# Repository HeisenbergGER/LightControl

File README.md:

# LightControl
Here you can find all project files for the LightControl Project, including schematics, PCB-designs, fabrication files and renderings.

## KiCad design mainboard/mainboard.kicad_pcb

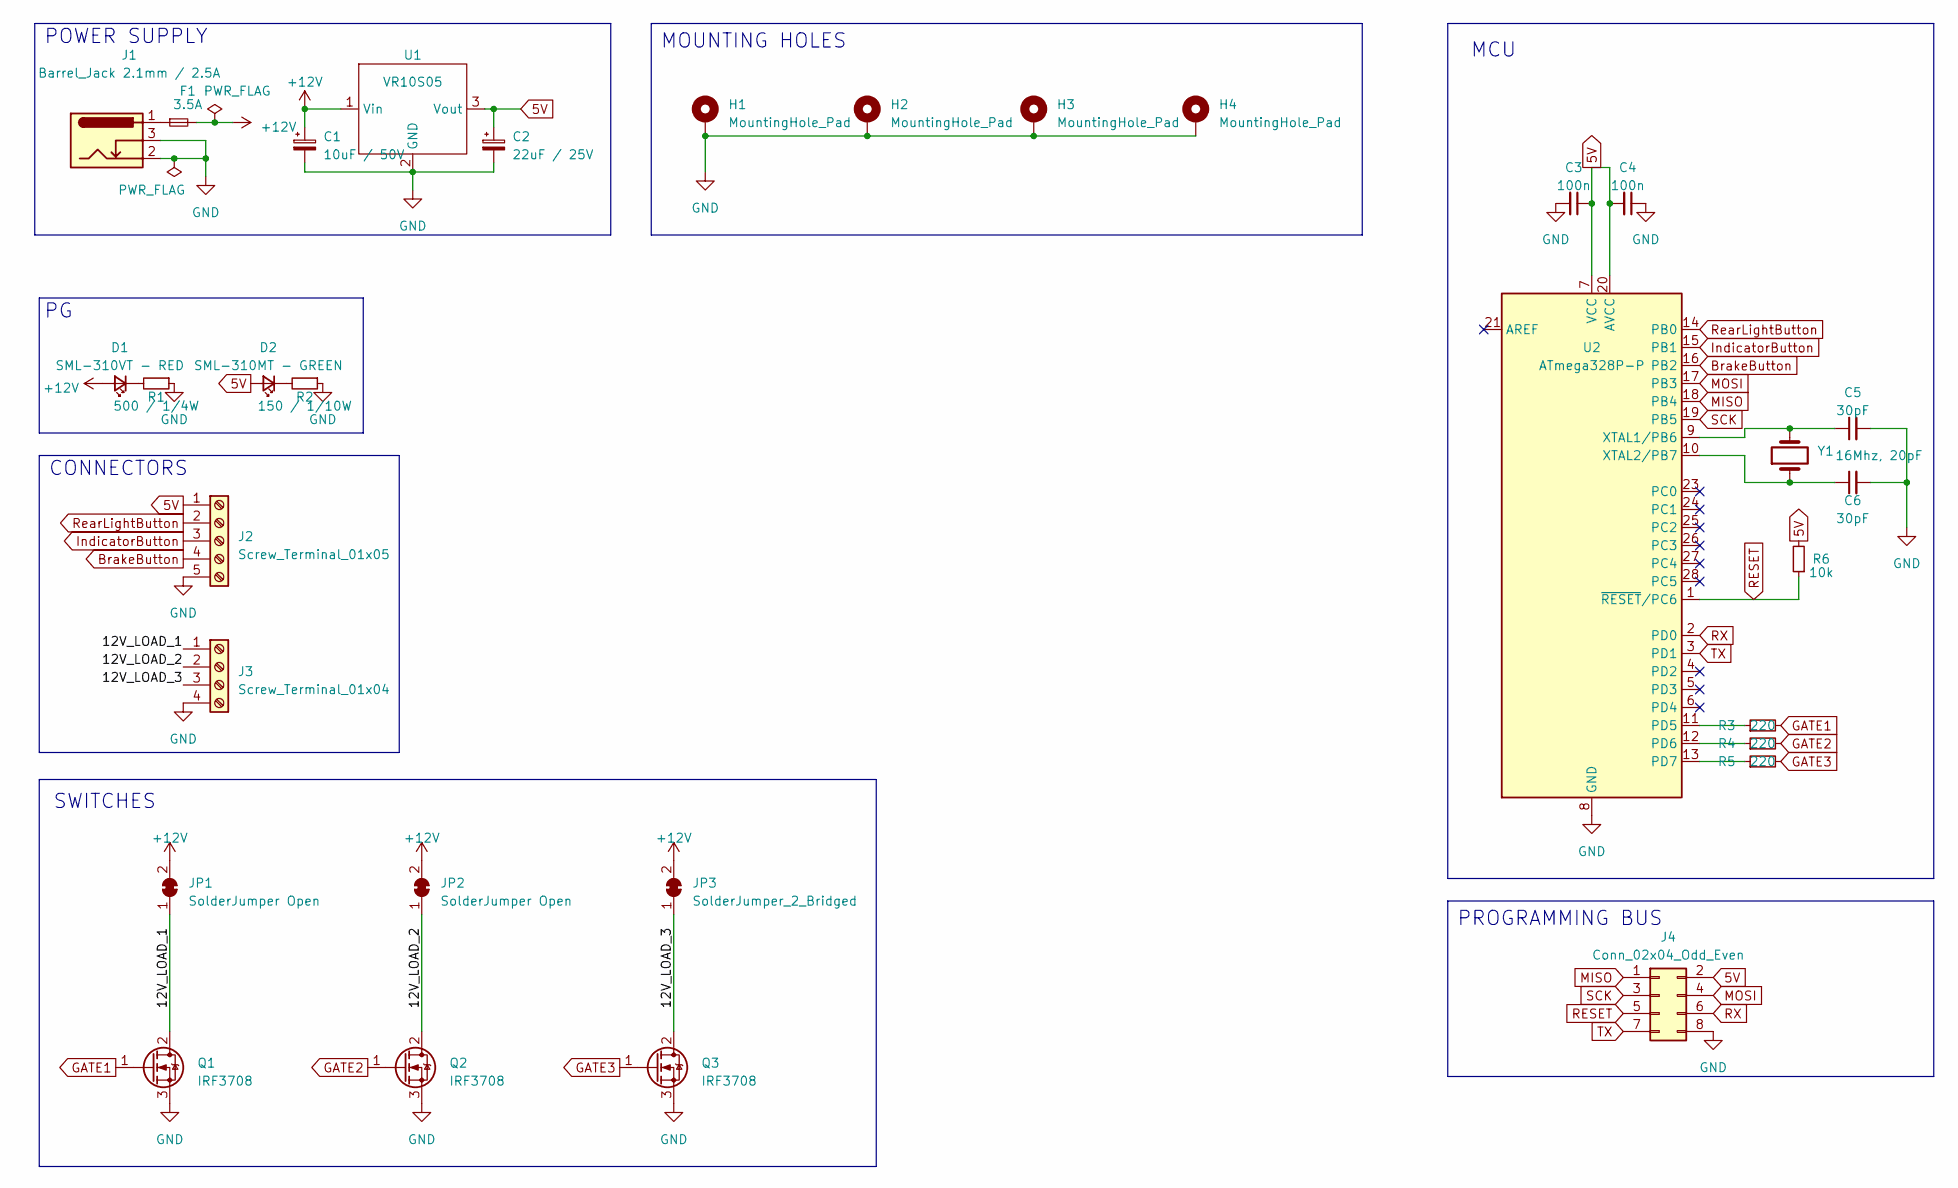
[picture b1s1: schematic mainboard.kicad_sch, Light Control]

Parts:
C1: 10uF / 50V; C_Radial_D5.0mm_H5.0mm_P2.00mm
C2: 22uF / 25V; C_Radial_D5.0mm_H5.0mm_P2.00mm
C3, C4: 100n; C_0603_1608Metric
C5, C6: 30pF; C_0603_1608Metric
D1: SML-310VT - RED; LED_0603_1608Metric
D2: SML-310MT - GREEN; LED_0603_1608Metric
F1: 3.5A; R_1206_3216Metric
H1, H2, H3, H4: MountingHole_Pad; MountingHole_3.2mm_M3_DIN965_Pad
J1: Barrel_Jack 2.1mm / 2.5A; CUI_PJ-202B
J2: Screw_Terminal_01x05; TerminalBlock_TE_282834-5_1x05_P2.54mm_Horizontal
J3: Screw_Terminal_01x04; TerminalBlock_TE_282834-4_1x04_P2.54mm_Horizontal
J4: Conn_02x04_Odd_Even; PinHeader_2x04_P2.54mm_Vertical
JP1, JP2: SolderJumper Open; SolderJumper-2_P1.3mm_Open_TrianglePad1.0x1.5mm
JP3: SolderJumper_2_Bridged; SolderJumper-2_P1.3mm_Open_TrianglePad1.0x1.5mm
Q1, Q2, Q3: IRF3708; TO-220-3_Vertical
R1: 500 / 1/4W; R_0603_1608Metric
R2: 150 / 1/10W; R_0603_1608Metric
R3, R4, R5: 220; R_0603_1608Metric
R6: 10k; R_0603_1608Metric
U1: VR10S05; SIP3_11.6x8.5mm
U2: ATmega328P-P; DIP-28_W7.62mm
Y1: 16Mhz, 20pF; Crystal_HC49-4H_Vertical

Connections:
5V: C2.1, C3.1, C4.2, D2.2 (A), J2.1, J4.2, R6.2, U1.3 (Vout), U2.7 (VCC), U2.20 (AVCC)
+12V: C1.1, D1.2 (A), F1.2, JP1.2 (B), JP2.2 (B), JP3.2 (B), U1.1 (Vin)
/12V_LOAD_1: J3.1, JP1.1 (A), Q1.2 (D)
/12V_LOAD_2: J3.2, JP2.1 (A), Q2.2 (D)
/12V_LOAD_3: J3.3, JP3.1 (A), Q3.2 (D)
BrakeButton: J2.4, U2.16 (PB2)
GATE1: Q1.1 (G), R3.2
GATE2: Q2.1 (G), R4.2
GATE3: Q3.1 (G), R5.2
GND: C1.2, C2.2, C3.2, C4.1, C5.2, C6.2, H1.1, H2.1, H3.1, H4.1, J1.2, J1.3, J2.5, J3.4, J4.8, Q1.3 (S), Q2.3 (S), Q3.3 (S), R1.1, R2.1, U1.2 (GND), U2.8 (GND), U2.22 (GND)
IndicatorButton: J2.3, U2.15 (PB1)
MISO: J4.1, U2.18 (PB4)
MOSI: J4.4, U2.17 (PB3)
unnamed: D1.1 (K), R1.2
unnamed: D2.1 (K), R2.2
unnamed: F1.1, J1.1
unnamed: R3.1, U2.11 (PD5)
unnamed: R4.1, U2.12 (PD6)
unnamed: R5.1, U2.13 (PD7)
unnamed: C5.1, U2.9 (XTAL1/PB6), Y1.2
unnamed: C6.1, U2.10 (XTAL2/PB7), Y1.1
RESET: J4.5, R6.1, U2.1 (~RESET/PC6)
RX: J4.6, U2.2 (PD0)
RearLightButton: J2.2, U2.14 (PB0)
SCK: J4.3, U2.19 (PB5)
TX: J4.7, U2.3 (PD1)

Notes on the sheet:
PROGRAMMING BUS
CONNECTORS
POWER SUPPLY
MOUNTING HOLES
SWITCHES
MCU

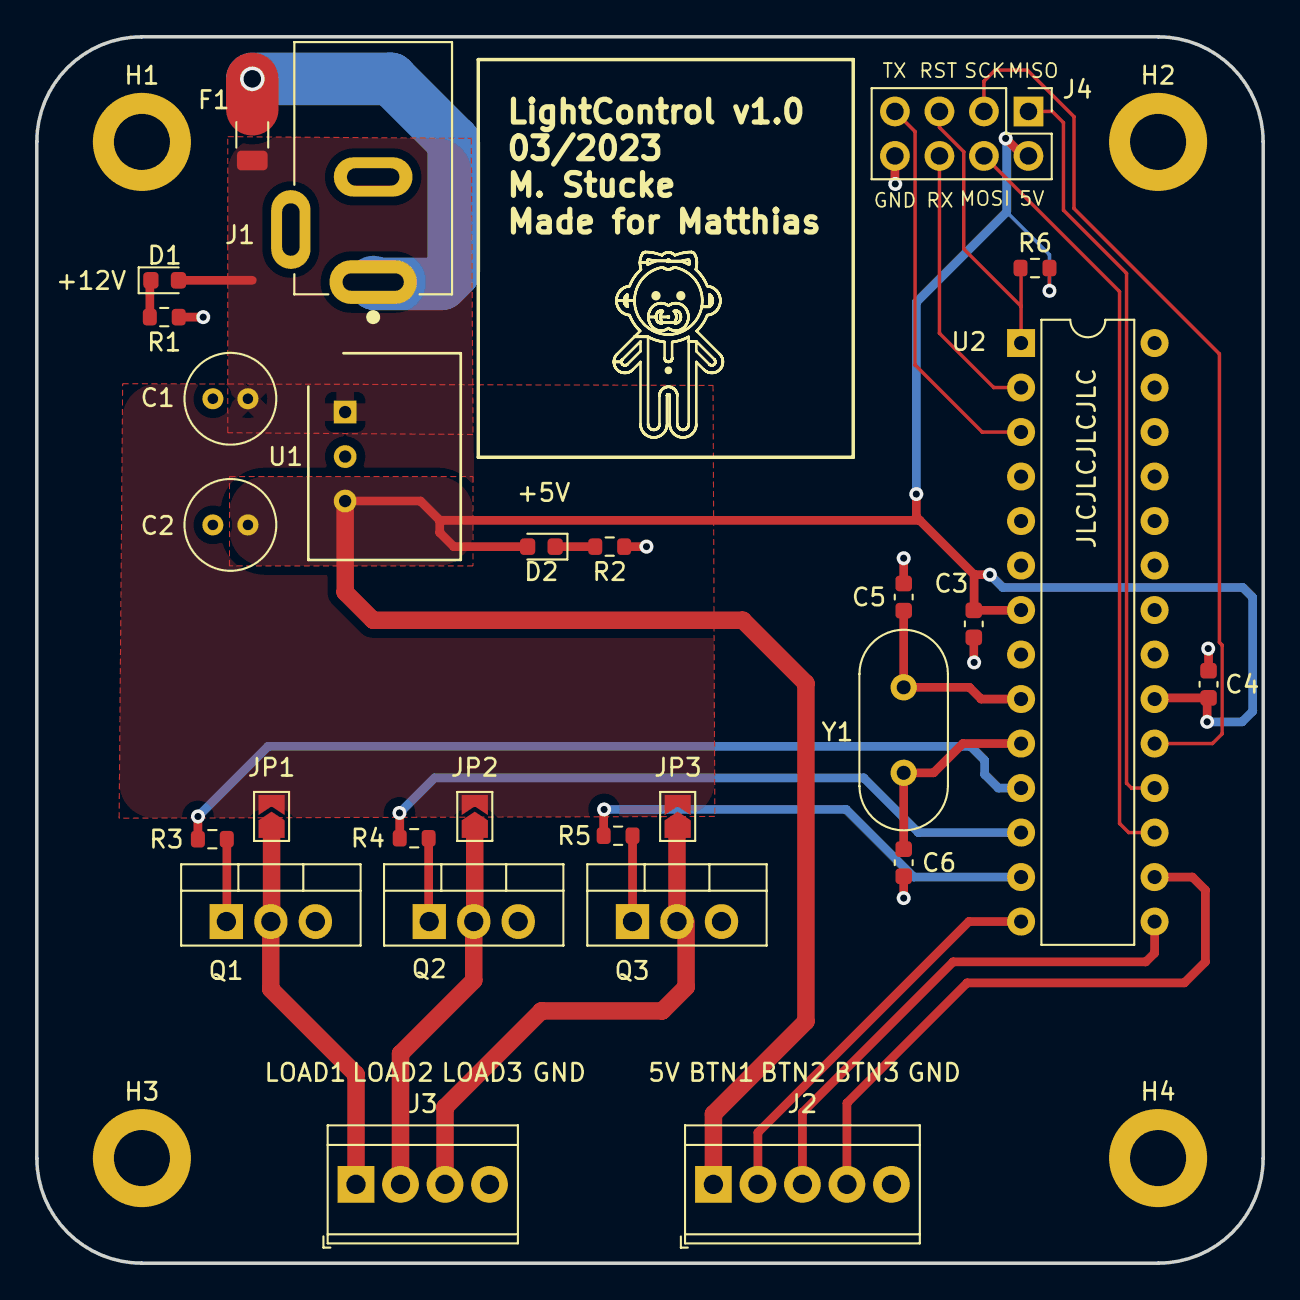
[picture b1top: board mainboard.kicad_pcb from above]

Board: 2 copper layers, 70.0 x 70.0 mm, 32 parts (0 on the bottom side), 26 nets.

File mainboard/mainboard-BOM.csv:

"ID";"Bezeichner";"Footprint";"Stückzahl";"Bezeichnung";"Anbieter und Referenz";
1;"C5,C6";"C_0603_1608Metric";2;"30pF";;;
2;"H4,H2,H3,H1";"MountingHole_3.2mm_M3_DIN965_Pad";4;"MountingHole_Pad";;;
3;"C3,C4";"C_0603_1608Metric";2;"100n";;;
4;"JP1,JP2";"SolderJumper-2_P1.3mm_Open_TrianglePad1.0x1.5mm";2;"SolderJumper Open";;;
5;"R5,R4,R3";"R_0603_1608Metric";3;"220";;;
6;"U2";"DIP-28_W7.62mm";1;"ATmega328P-P";;;
7;"Q3,Q1,Q2";"TO-220-3_Vertical";3;"IRF3708";;;
8;"J1";"CUI_PJ-202B";1;"Barrel_Jack 2.1mm / 2.5A";;;
9;"R1";"R_0603_1608Metric";1;"500 / 1/4W";;;
10;"D1";"LED_0603_1608Metric";1;"SML-310VT - RED";;;
11;"J4";"PinHeader_2x04_P2.54mm_Vertical";1;"Conn_02x04_Odd_Even";;;
12;"J3";"TerminalBlock_TE_282834-4_1x04_P2.54mm_Horizontal";1;"Screw_Terminal_01x04";;;
13;"U1";"SIP3_11.6x8.5mm";1;"VR10S05";;;
14;"J2";"TerminalBlock_TE_282834-5_1x05_P2.54mm_Horizontal";1;"Screw_Terminal_01x05";;;
15;"JP3";"SolderJumper-2_P1.3mm_Open_TrianglePad1.0x1.5mm";1;"SolderJumper_2_Bridged";;;
16;"C1";"C_Radial_D5.0mm_H5.0mm_P2.00mm";1;"10uF / 50V";;;
17;"D2";"LED_0603_1608Metric";1;"SML-310MT - GREEN";;;
18;"F1";"R_1206_3216Metric";1;"3.5A";;;
19;"R6";"R_0603_1608Metric";1;"10k";;;
20;"Y1";"Crystal_HC49-4H_Vertical";1;"16Mhz, 20pF";;;
21;"C2";"C_Radial_D5.0mm_H5.0mm_P2.00mm";1;"22uF / 25V";;;
22;"R2";"R_0603_1608Metric";1;"150 / 1/10W";;;

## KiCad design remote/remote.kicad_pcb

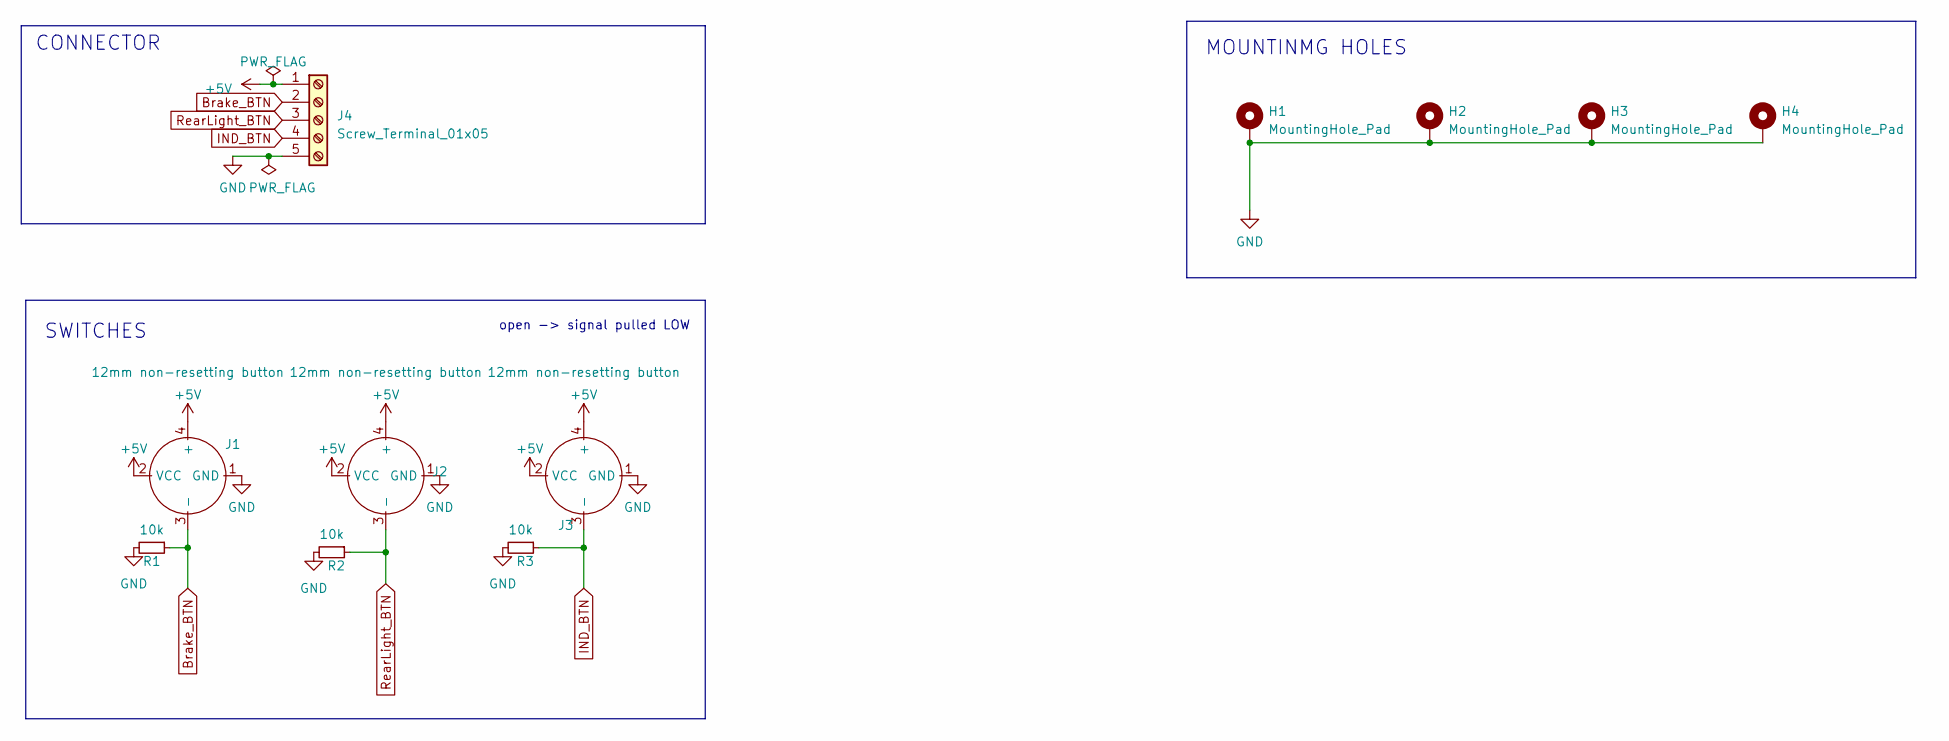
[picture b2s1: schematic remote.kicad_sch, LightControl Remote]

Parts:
H1, H2, H3, H4: MountingHole_Pad; MountingHole_3.2mm_M3_DIN965_Pad
J1, J2, J3: 12mm non-resetting button; 5V_LED_BTN
J4: Screw_Terminal_01x05; TerminalBlock_TE_282834-5_1x05_P2.54mm_Horizontal
R1, R2, R3: 10k; R_0603_1608Metric

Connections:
+5V: J1.2 (VCC), J1.4 (+), J2.2 (VCC), J2.4 (+), J3.2 (VCC), J3.4 (+), J4.1
Brake_BTN: J1.3 (-), J4.2, R1.1
GND: H1.1, H2.1, H3.1, H4.1, J1.1 (GND), J2.1 (GND), J3.1 (GND), J4.5, R1.2, R2.2, R3.2
IND_BTN: J3.3 (-), J4.4, R3.1
RearLight_BTN: J2.3 (-), J4.3, R2.1

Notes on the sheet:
CONNECTOR
open -> signal pulled LOW
SWITCHES
MOUNTINMG HOLES

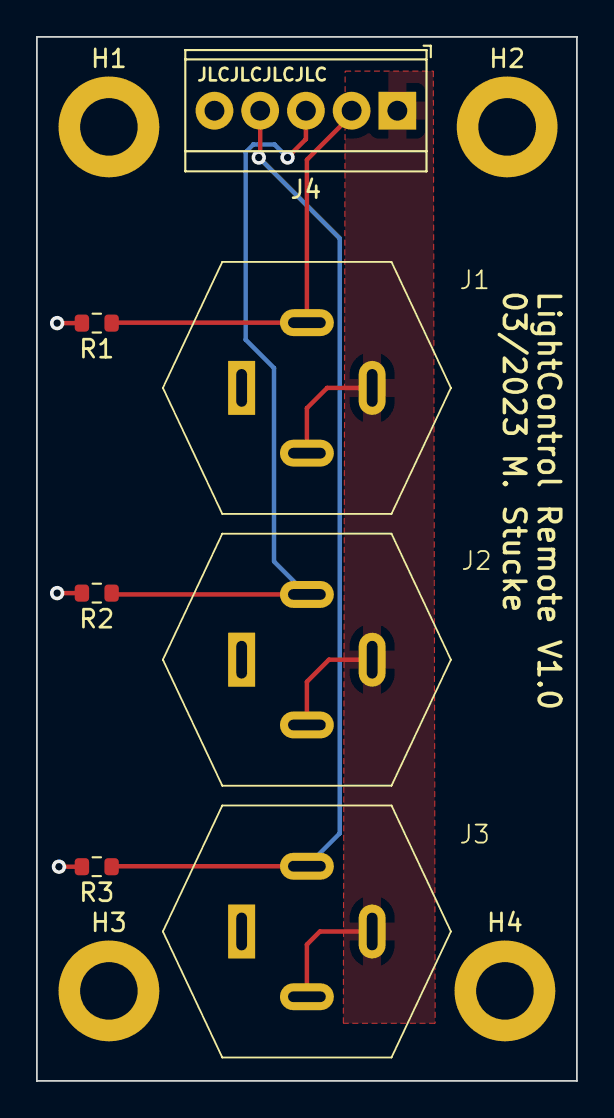
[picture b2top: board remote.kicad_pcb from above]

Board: 2 copper layers, 30.0 x 58.0 mm, 11 parts (0 on the bottom side), 5 nets.

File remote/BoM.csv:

"ID";"Bezeichner";"Footprint";"Stückzahl";"Bezeichnung";"Anbieter und Referenz";
1;"H1,H3,H4,H2";"MountingHole_3.2mm_M3_DIN965_Pad";4;"MountingHole_Pad";;;
2;"R1,R2,R3";"R_0603_1608Metric";3;"10k";;;
3;"J1,J2,J3";"5V_LED_BTN";3;"12mm non-resetting button";;;
4;"J4";"TerminalBlock_TE_282834-5_1x05_P2.54mm_Horizontal";1;"Screw_Terminal_01x05";;;

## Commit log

2023-03-24 Minor fixes
2023-03-24 added documentation and qr-code
2023-03-24 added fuse, modified trace widths and added fabrication files
2023-03-24 updated BOM
2023-03-24 minor changes
2023-03-24 Added first Code
2023-03-29 generated new fabrication files
